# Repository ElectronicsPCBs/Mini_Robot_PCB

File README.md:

# Mini_Robot_PCB
A robot on PCB

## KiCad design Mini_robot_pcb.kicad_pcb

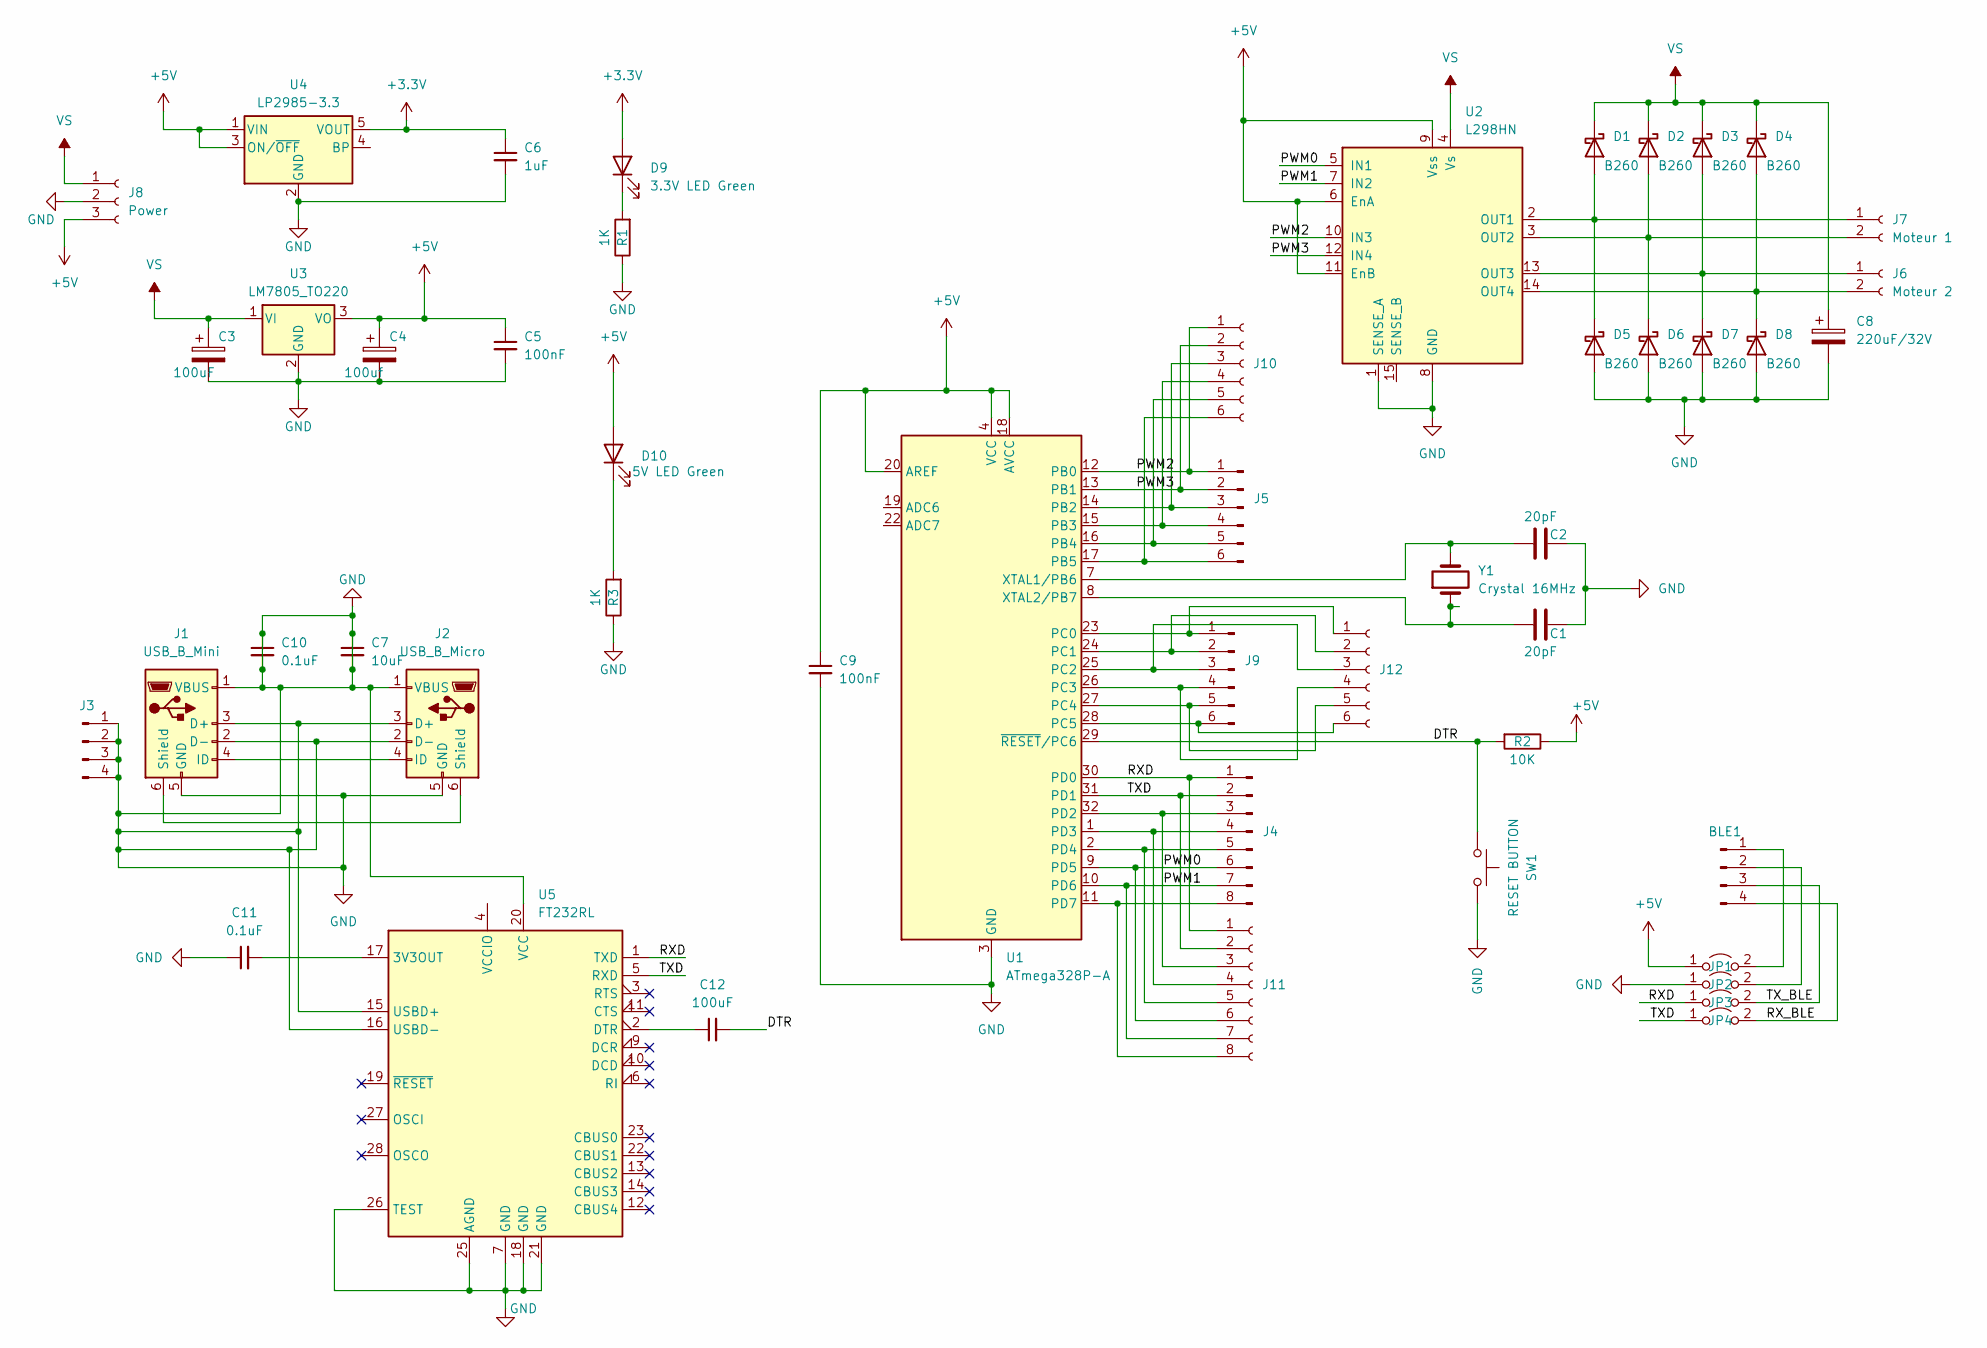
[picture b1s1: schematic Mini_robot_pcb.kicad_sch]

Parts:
BLE1: Conn_01x04_Pin; PinSocket_1x04_P2.54mm_Vertical
C1, C2: 20pF; C_0805_2012Metric_Pad1.18x1.45mm_HandSolder
C3: 100uF; CP_Radial_D8.0mm_P3.50mm
C4: 100uf; CP_Radial_D8.0mm_P3.50mm
C5, C9: 100nF; C_0805_2012Metric_Pad1.18x1.45mm_HandSolder
C6: 1uF; C_0805_2012Metric_Pad1.18x1.45mm_HandSolder
C7: 10uF; C_0805_2012Metric_Pad1.18x1.45mm_HandSolder
C8: 220uF/32V; CP_Radial_D8.0mm_P3.50mm
C10, C11: 0.1uF; C_0805_2012Metric_Pad1.18x1.45mm_HandSolder
C12: 100uF; C_0805_2012Metric_Pad1.18x1.45mm_HandSolder
D1, D2, D3, D4, D5, D6, D7, D8: B260; D_SMB
D9: 3.3V LED Green; LED_0805_2012Metric_Pad1.15x1.40mm_HandSolder
D10: 5V LED Green; LED_0805_2012Metric_Pad1.15x1.40mm_HandSolder
J1: USB_B_Mini; USB_Mini-B_Lumberg_2486_01_Horizontal
J2: USB_B_Micro; USB_Micro-B_Molex-105017-0001
J3: Conn_01x04_Pin; PinSocket_1x04_P2.54mm_Vertical
J4: Conn_01x08_Pin; PinSocket_1x08_P2.54mm_Vertical
J5, J9: Conn_01x06_Pin; PinSocket_1x06_P2.54mm_Vertical
J6: Moteur 2; TerminalBlock_Altech_AK300-2_P5.00mm
J7: Moteur 1; TerminalBlock_Altech_AK300-2_P5.00mm
J8: Power; TerminalBlock_Altech_AK300-3_P5.00mm
J10, J12: Conn_01x06_Socket; PinHeader_1x06_P2.54mm_Vertical
J11: Conn_01x08_Socket; PinHeader_1x08_P2.54mm_Vertical
JP1, JP2, JP3, JP4: Jumper_2_Open; SolderJumper-2_P1.3mm_Open_Pad1.0x1.5mm
R1, R3: 1K; R_0805_2012Metric_Pad1.20x1.40mm_HandSolder
R2: 10K; R_0805_2012Metric_Pad1.20x1.40mm_HandSolder
SW1: RESET BUTTON; SW_Push_1P1T_NO_6x6mm_H9.5mm
U1: ATmega328P-A; TQFP-32_7x7mm_P0.8mm
U2: L298HN; TO-220-15_P2.54x2.54mm_StaggerOdd_Lead5.84mm_TabDown
U3: LM7805_TO220; TO-220-3_Vertical
U4: LP2985-3.3; SOT-23-5
U5: FT232RL; SSOP-28_5.3x10.2mm_P0.65mm
Y1: Crystal 16MHz; Crystal_HC49-U_Vertical

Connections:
+3.3V: C6.1, D9.2 (A), U4.5 (VOUT)
+5V: C4.1, C5.1, C9.1, D10.2 (A), J8.3, JP1.1 (A), R2.1, U1.4 (VCC), U1.6 (VCC), U1.18 (AVCC), U1.20 (AREF), U2.6 (EnA), U2.9 (Vss), U2.11 (EnB), U3.3 (VO), U4.1 (VIN), U4.3 (ON/~OFF)
/DTR: C12.2, R2.2, SW1.1, U1.29 (~RESET/PC6)
/PWM2: J5.1, J10.1, U1.12 (PB0), U2.10 (IN3)
/PWM3: J5.2, J10.2, U1.13 (PB1), U2.12 (IN4)
/RXD: J4.1, J11.1, JP3.1 (A), U1.30 (PD0), U5.1 (TXD)
/RX_BLE: BLE1.4, JP4.2 (B)
/TXD: J4.2, J11.2, JP4.1 (A), U1.31 (PD1), U5.5 (RXD)
/TX_BLE: BLE1.3, JP3.2 (B)
GND: C1.1, C2.2, C3.2, C4.2, C5.2, C6.2, C7.1, C7.2, C8.2, C9.2, C10.1, C10.2, C11.1, D5.2 (A), D6.2 (A), D7.2 (A), D8.2 (A), J1.1 (VBUS), J1.2 (D-), J1.3 (D+), J1.5 (GND), J2.1 (VBUS), J2.2 (D-), J2.3 (D+), J2.5 (GND), J3.1, J3.2, J3.3, J3.4, J8.2, JP2.1 (A), R1.1, R3.1, SW1.2, U1.3 (GND), U1.5 (GND), U1.21 (GND), U2.1 (SENSE_A), U2.8 (GND), U3.2 (GND), U4.2 (GND), U5.7 (GND), U5.15 (USBD+), U5.16 (USBD-), U5.18 (GND), U5.20 (VCC), U5.21 (GND), U5.25 (AGND), U5.26 (TEST)
unnamed: BLE1.1, JP1.2 (B)
unnamed: BLE1.2, JP2.2 (B)
unnamed: D1.2 (A), D5.1 (K), J7.1, U2.2 (OUT1)
unnamed: D2.2 (A), D6.1 (K), J7.2, U2.3 (OUT2)
unnamed: D3.2 (A), D7.1 (K), J6.1, U2.13 (OUT3)
unnamed: D4.2 (A), D8.1 (K), J6.2, U2.14 (OUT4)
unnamed: D9.1 (K), R1.2
unnamed: D10.1 (K), R3.2
unnamed: J1.4 (ID), J2.4 (ID)
unnamed: J1.6 (Shield), J2.6 (Shield)
unnamed: J5.3, J10.3, U1.14 (PB2)
unnamed: J5.4, J10.4, U1.15 (PB3)
unnamed: J5.5, J10.5, U1.16 (PB4)
unnamed: J5.6, J10.6, U1.17 (PB5)
unnamed: J4.4, J11.4, U1.1 (PD3)
unnamed: J4.5, J11.5, U1.2 (PD4)
unnamed: J4.8, J11.8, U1.11 (PD7)
unnamed: J9.1, J12.1, U1.23 (PC0)
unnamed: J9.2, J12.2, U1.24 (PC1)
unnamed: J9.3, J12.3, U1.25 (PC2)
unnamed: J9.4, J12.4, U1.26 (PC3)
unnamed: J9.5, J12.5, U1.27 (PC4)
unnamed: J9.6, J12.6, U1.28 (PC5)
unnamed: C2.1, U1.7 (XTAL1/PB6), Y1.2
unnamed: C1.2, U1.8 (XTAL2/PB7), Y1.1
unnamed: C11.2, U5.17 (3V3OUT)
unnamed: C12.1, U5.2 (DTR)
VS: C3.1, C8.1, D1.1 (K), D2.1 (K), D3.1 (K), D4.1 (K), J8.1, U2.4 (Vs), U3.1 (VI)

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
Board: 2 copper layers, 49 parts (0 on the bottom side), 41 nets, no tracks yet.

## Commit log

2023-08-23 First progress
2023-08-23 Ignore backups
2023-09-17 Add bleutooth and FTDI
